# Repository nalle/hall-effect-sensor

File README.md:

# hall-effect-sensor
A Hall Effect measurement system for measuring power/amperage for graphing

This uses the circuit described in the eagle/gerber directory. 
We've used dirtypcbs.com to make them (http://dirtypcbs.com/view.php?share=27748&accesskey=)

The code used is in arduino/src
It is dependant on 
https://github.com/sirleech/TrueRandom
https://github.com/openenergymonitor/EmonLib 
https://github.com/ntruchsess/arduino_uip (which in turn is patched to support sending DHCP Client Identification which is why it is included in arduino/src)

Hall effect sensors used are SCT-013-000.

---------------------------------------------

IMPORTANT!!

When running on a 2k SRAM AVR (most arduinos) you will need to tweak the serial RX/TX buffers.
This can be found in Arduino/hardware/arduino/avr/cores/arduino/HardwareSerial.h

Just change 
#define SERIAL_TX_BUFFER_SIZE 64
to 
#define SERIAL_TX_BUFFER_SIZE 8

and 

#define SERIAL_RX_BUFFER_SIZE 64
to
#define SERIAL_RX_BUFFER_SIZE 8

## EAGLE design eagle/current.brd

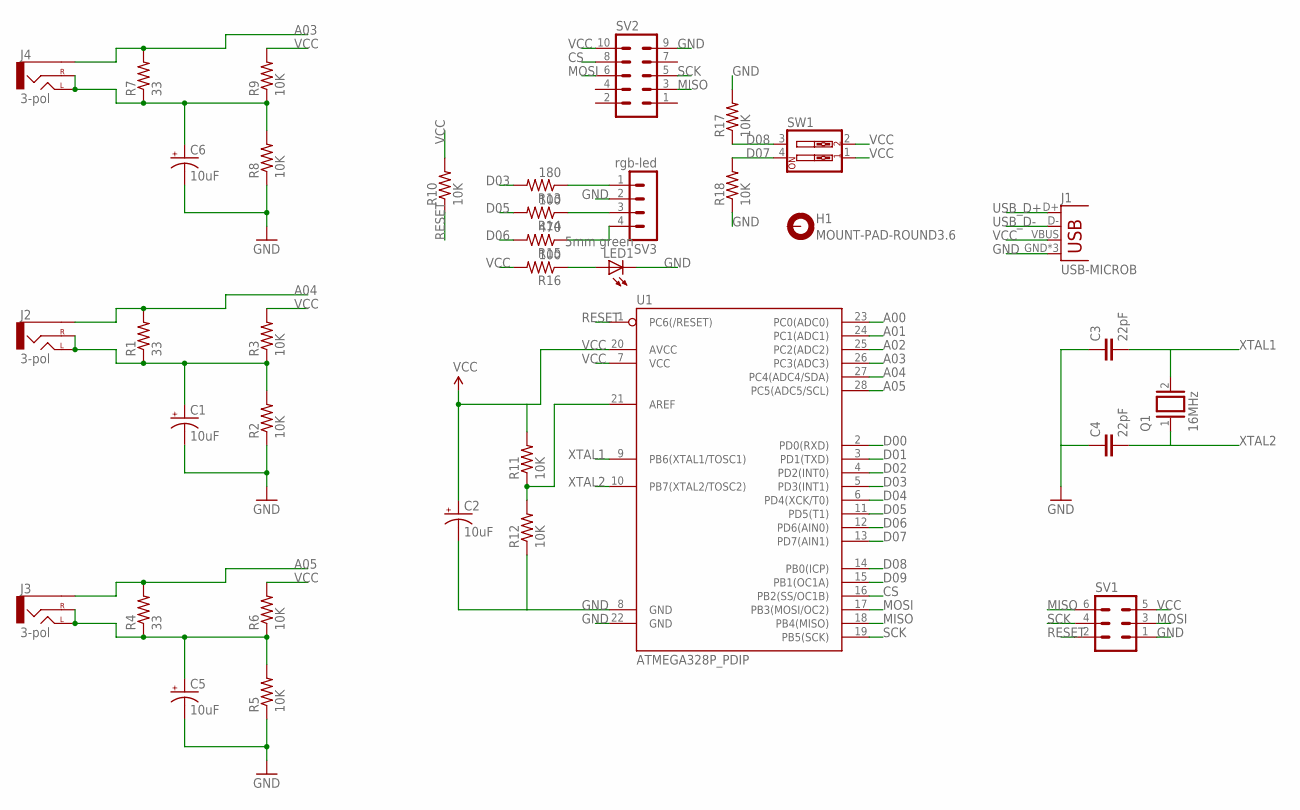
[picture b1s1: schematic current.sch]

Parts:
C1, C5, C6: 10uF; CPOL-RADIAL-100UF-25V
C2: 10uF; CPOL-RADIAL-10UF-25V
C3, C4: 22pF; C5B2.5
H1: MOUNT-PAD-ROUND3.6; 3,6-PAD
J1: USB-MICROB
J2, J3, J4: 3-pol; AUDIO-JACK
LED1: 5mm green; LED5MM
Q1: 16MHz; QS
R1, R4, R7: 33; 0204/5
R2, R3, R5, R6, R8, R9, R10, R11, R12, R17, R18: 10K; 0204/5
R13: 180; 0204/5
R14, R16: 100; 0204/5
R15: 470; 0204/5
SV1: MA03-2
SV2: MA05-2
SV3: rgb-led; MA04-1
SW1: SW_DIP-2; EDG-02
U1: ATMEGA328P_PDIP; DIL28-3

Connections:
A00: U1.23 (PC0(ADC0))
A01: U1.24 (PC1(ADC1))
A02: U1.25 (PC2(ADC2))
A03: J4.SLEEVE, R7.2, U1.26 (PC3(ADC3))
A04: J2.SLEEVE, R1.2, U1.27 (PC4(ADC4/SDA))
A05: J3.SLEEVE, R4.2, U1.28 (PC5(ADC5/SCL))
CS: SV2.8, U1.16 (PB2(SS/OC1B))
D00: U1.2 (PD0(RXD))
D01: U1.3 (PD1(TXD))
D02: U1.4 (PD2(INT0))
D03: R13.2, U1.5 (PD3(INT1))
D04: U1.6 (PD4(XCK/T0))
D05: R14.2, U1.11 (PD5(T1))
D06: R15.2, U1.12 (PD6(AIN0))
D07: R18.2, SW1.4, U1.13 (PD7(AIN1))
D08: R17.1, SW1.3, U1.14 (PB0(ICP))
D09: U1.15 (PB1(OC1A))
GND: C1.2 (-), C2.2 (-), C3.1, C4.1, C5.2 (-), C6.2 (-), J1.GND, J1.MT1 (GND), J1.MT2 (GND), LED1.K (C), R2.1, R5.1, R8.1, R12.1, R17.2, R18.1, SV1.1, SV2.9, U1.8 (GND), U1.22 (GND)
MISO: SV1.6, SV2.3, U1.18 (PB4(MISO))
MOSI: SV1.3, SV2.6, U1.17 (PB3(MOSI/OC2))
unnamed: C5.1 (+), J3.RING (RIGHT), J3.TIP (LEFT), R4.1, R5.2, R6.1
unnamed: C1.1 (+), J2.RING (RIGHT), J2.TIP (LEFT), R1.1, R2.2, R3.1
unnamed: C6.1 (+), J4.RING (RIGHT), J4.TIP (LEFT), R7.1, R8.2, R9.1
unnamed: R13.1, SV3.1
unnamed: R11.1, R12.2, U1.21 (AREF)
unnamed: R14.1, SV3.3
unnamed: R15.1, SV3.4
unnamed: LED1.A, R16.1
RESET: R10.1, SV1.2, U1.1 (PC6(/RESET))
SCK: SV1.4, SV2.5, U1.19 (PB5(SCK))
USB_D+: J1.D+
USB_D-: J1.D-
VCC: C2.1 (+), J1.VBUS, R3.2, R6.2, R9.2, R10.2, R11.2, R16.2, SV1.5, SV2.10, SW1.1, SW1.2, U1.7 (VCC), U1.20 (AVCC)
XTAL1: C3.2, Q1.2, U1.9 (PB6(XTAL1/TOSC1))
XTAL2: C4.2, Q1.1, U1.10 (PB7(XTAL2/TOSC2))

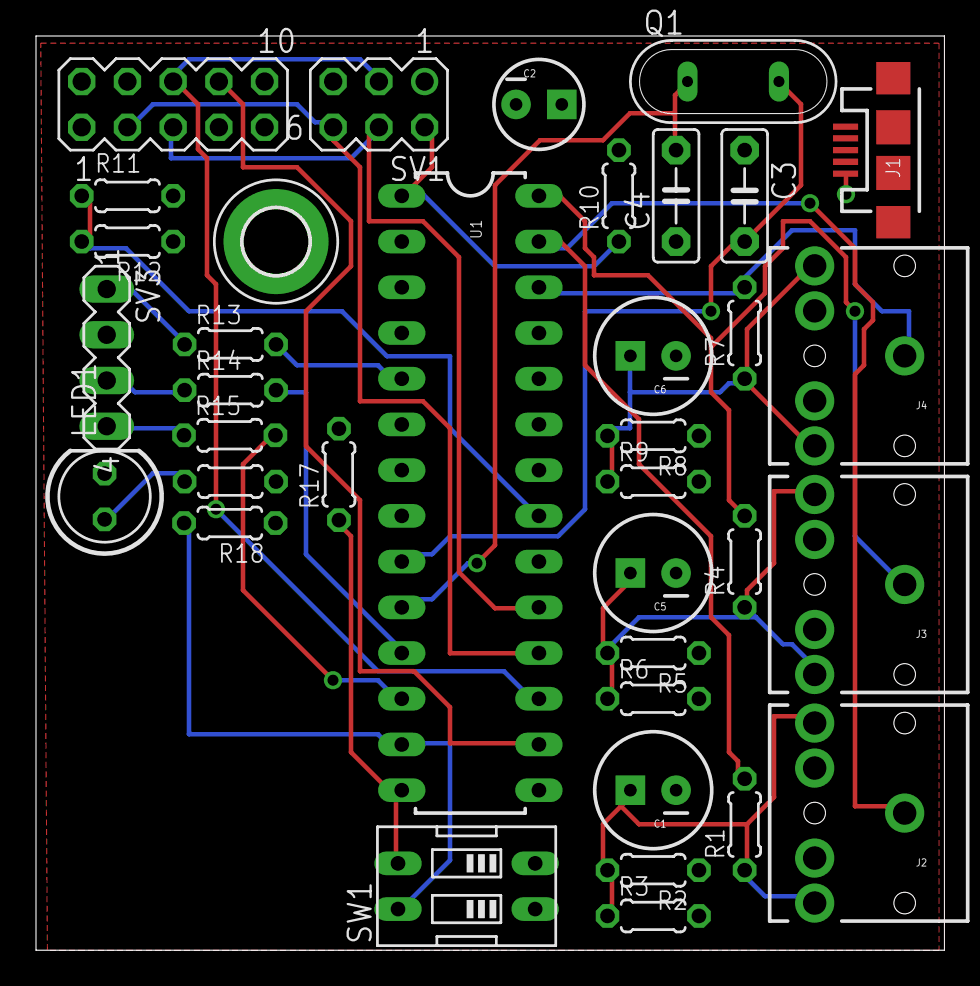
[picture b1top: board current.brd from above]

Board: 2 copper layers, 50.5 x 50.8 mm, 36 parts (0 on the bottom side), 25 nets.

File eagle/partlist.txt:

Partlist

Exported from current.sch at 2016-11-06 10:24

EAGLE Version 7.7.0 Copyright (c) 1988-2016 CadSoft

Assembly variant: 

Part     Value              Device             Package               Library             Sheet

C1       10uF               CAP_POLPTH1        CPOL-RADIAL-100UF-25V SparkFun-Passives   1
C2       10uF               CAP_POLPTH2        CPOL-RADIAL-10UF-25V  SparkFun-Capacitors 1
C3       22pF               C5/2.5             C5B2.5                capacitor-wima      1
C4       22pF               C5/2.5             C5B2.5                capacitor-wima      1
C5       10uF               CAP_POLPTH1        CPOL-RADIAL-100UF-25V SparkFun-Passives   1
C6       10uF               CAP_POLPTH1        CPOL-RADIAL-100UF-25V SparkFun-Passives   1
H1       MOUNT-PAD-ROUND3.6 MOUNT-PAD-ROUND3.6 3,6-PAD               holes               1
J1       USB-MICROB         USB-MICROB         USB-MICROB            SparkFun-Connectors 1
J2       3-pol              AUDIO-JACKPTH      AUDIO-JACK            SparkFun-Connectors 1
J3       3-pol              AUDIO-JACKPTH      AUDIO-JACK            SparkFun-Connectors 1
J4       3-pol              AUDIO-JACKPTH      AUDIO-JACK            SparkFun-Connectors 1
LED1     5mm green          LED5MM             LED5MM                led                 1
Q1       16MHz              XTAL/S             QS                    special             1
R1       33                 R-US_0204/5        0204/5                resistor            1
R2       10K                R-US_0204/5        0204/5                resistor            1
R3       10K                R-US_0204/5        0204/5                resistor            1
R4       33                 R-US_0204/5        0204/5                resistor            1
R5       10K                R-US_0204/5        0204/5                resistor            1
R6       10K                R-US_0204/5        0204/5                resistor            1
R7       33                 R-US_0204/5        0204/5                resistor            1
R8       10K                R-US_0204/5        0204/5                resistor            1
R9       10K                R-US_0204/5        0204/5                resistor            1
R10      10K                R-US_0204/5        0204/5                resistor            1
R11      10K                R-US_0204/5        0204/5                resistor            1
R12      10K                R-US_0204/5        0204/5                resistor            1
R13      180                R-US_0204/5        0204/5                resistor            1
R14      100                R-US_0204/5        0204/5                resistor            1
R15      470                R-US_0204/5        0204/5                resistor            1
R16      100                R-US_0204/5        0204/5                resistor            1
R17      10K                R-US_0204/5        0204/5                resistor            1
R18      10K                R-US_0204/5        0204/5                resistor            1
SV1                         MA03-2             MA03-2                con-lstb            1
SV2                         MA05-2             MA05-2                con-lstb            1
SV3      rgb-led            MA04-1             MA04-1                con-lstb            1
SW1                         SW_DIP-2           EDG-02                special             1
U1       ATMEGA328P_PDIP    ATMEGA328P_PDIP    DIL28-3               SparkFun-DigitalIC  1

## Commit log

2016-11-07 Added the initial code for the sensor circuit
2016-11-07 Short description of the project
2016-11-07 Added links to dependencys
2016-11-08 Added schematics and gerber files for the sensor board
2016-11-08 Feature: Sending custom clientId option in DHCP request, requires the attached UIPEthernet Library
2016-11-08 Optimized output and fixed millis() overflow wrap
2016-11-08 Getting clientId option data dynamically from macaddress
2016-11-08 Ran autoformat on code due to different tabspaces being used
2016-11-08 Changed client-hostname to begin with PP
2016-11-08 Example for HTTP response
2016-11-09 Removed if statement for catching options we don't use
2016-11-09 On popular request (;D) switched over to HTTP as response and hopefully solved the rollover problem
2016-11-09 Optimized memory allocation as we are running very close to 2048 bytes
2016-11-09 More memory optimizations
2016-11-10 Added reference to why UIPEthernet is included and where the original can be found
2016-11-10 I keep forgetting these settings so now they're commited with everything else
2016-11-11 BUG: On re-transmits there is a chance the ENC28J60 circuit hangs, this is the recommended fix from Microchip
2016-11-11 Addressed issues #5 and #6
    Issue #5 - Implemented RESET and the AC/DC choice
    RESET is both channels on and then we fall back into AC (remember that
    if the switches are not flipped back it will reset MAC every boot)
    AC is both off and default fallback if no AC or DC choice was made
    DC is first channel on and second off
    Issse #6 - Implemented LOADING, ERROR and OK colors
2016-11-13 Tidy up for reset code
2016-11-15 Changed to the prometheus format as that is what will be used for our project
2016-11-15 Updated README with tips on memory optimization for 2k SRAM AVRs
2016-11-24 Converting float to string with decimals to measure in A instead of mA
2016-11-24 Corrected fuse and cpu configuration to make the m328p run at 16mhz with the external clock

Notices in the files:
parts and their libraries:
SparkFun-Connectors: Licensing: Creative Commons ShareAlike 4.0 International - https://creativecommons.org/licenses/by-sa/4.0
